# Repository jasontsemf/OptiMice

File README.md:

# OptiMice

## Intro

> "Bespoke computer mice powered by AI and 3D printing"

[Learn more about the project](https://jasontsemf.github.io/optimice.html) on Jason's portfolio site

## Complementary Web Platform

[Live on Back4App](https://optimice-jasontsemf.b4a.run).

[GitHub Repo](https://github.com/jasontsemf/OptimiceDashboard) of the web platform

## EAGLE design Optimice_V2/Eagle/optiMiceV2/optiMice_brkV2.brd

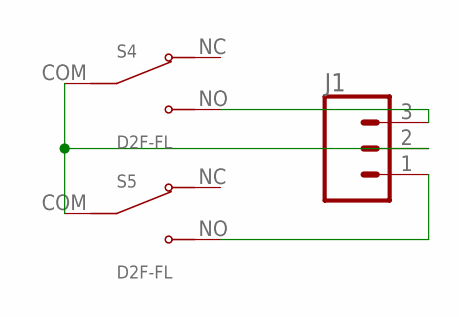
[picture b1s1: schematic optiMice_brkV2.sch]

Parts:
J1: CONN_03JST-PTH-VERT; JST-3-PTH-VERT
S4, S5: D2F-FL; SW_D2F-FL

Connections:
unnamed: J1.2, S4.COM, S5.COM
unnamed: J1.3, S4.NO
unnamed: J1.1, S5.NO

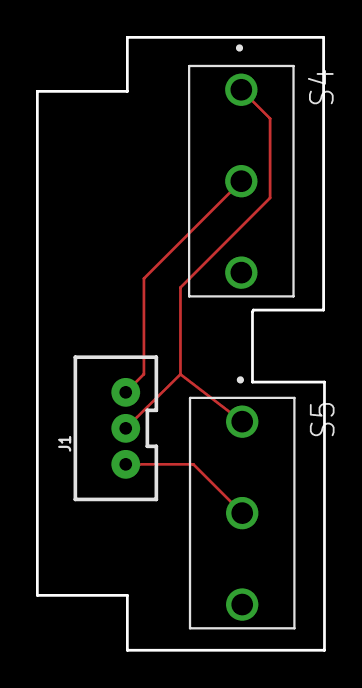
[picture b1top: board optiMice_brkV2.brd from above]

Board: 2 copper layers, 15.9 x 34.0 mm, 3 parts (0 on the bottom side), 3 nets.

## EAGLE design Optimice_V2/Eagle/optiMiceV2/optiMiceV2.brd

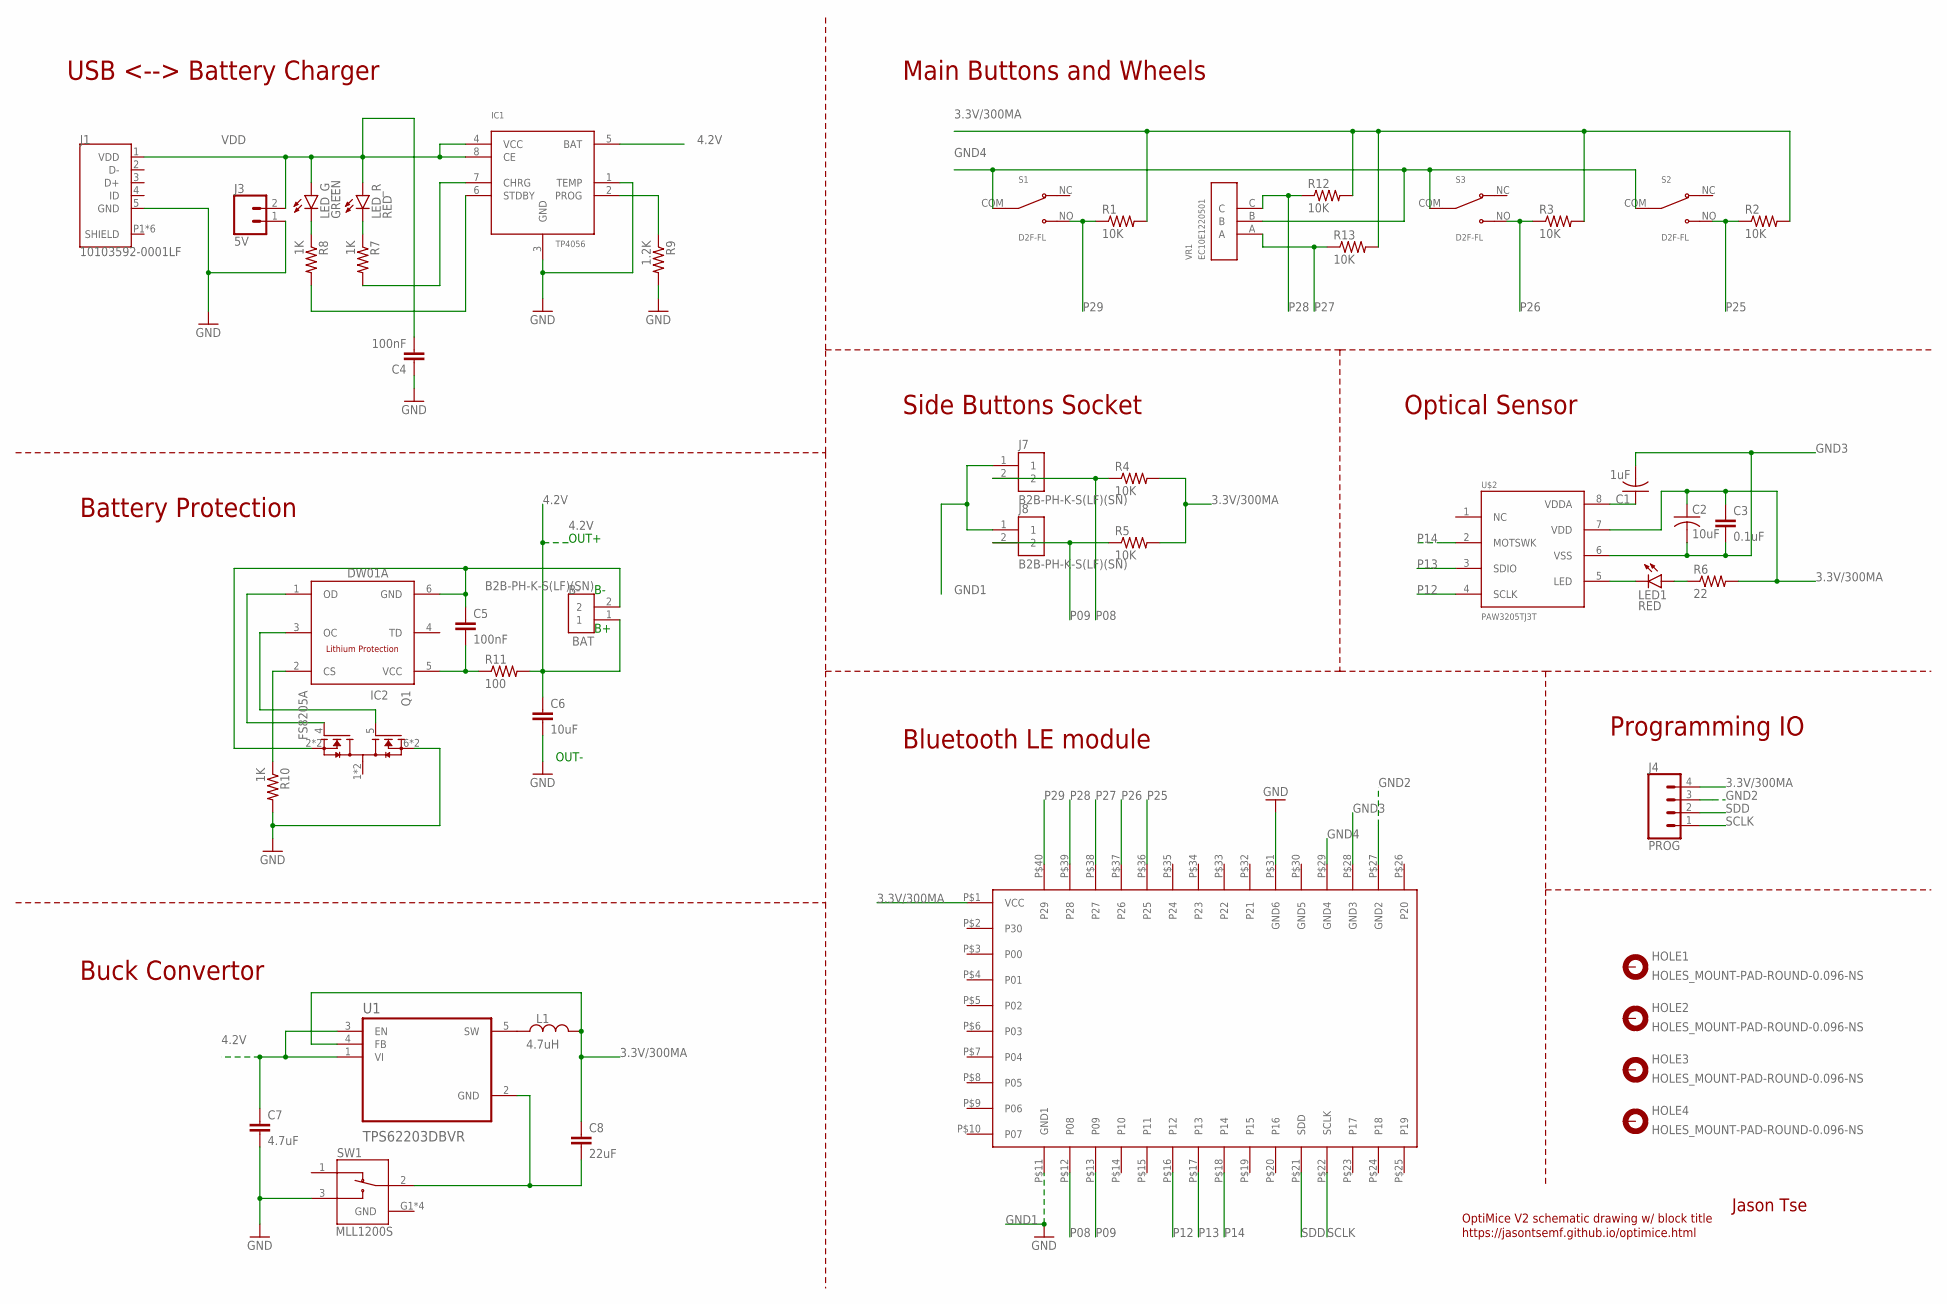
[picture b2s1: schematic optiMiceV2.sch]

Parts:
BAT: B2B-PH-K-S(LF)(SN); JST_B2B-PH-K-S(LF)(SN)
C1: 1uF; C0805K
C2: 10uF; C0805K
C3: 0.1uF; C0805K
C4, C5: 100nF; C0805
C6: 10uF; C0805
C7: 4.7uF; C0805
C8: 22uF; C0805
HOLE1, HOLE2, HOLE3, HOLE4: HOLES_MOUNT-PAD-ROUND-0.096-NS; HOLES_096-PAD-NS
IC1: TP4056; SOP-8
IC2: DW01A; SOT23-6
J1: 10103592-0001LF; AMPHENOL_10103592-0001LF
J3: 5V; 1X02
J4: PROG; 1X04
J7, J8: B2B-PH-K-S(LF)(SN); JST_B2B-PH-K-S(LF)(SN)
L1: 4.7uH; INDC2009X120
LED1: RED; LED5MM
LED_G: GREEN; CHIP-LED0805
LED_R: RED; CHIP-LED0805
Q1: FS8205A; SOP65P640X120-8N
R1, R2, R3, R4, R5, R12, R13: 10K; R0805
R6: 22; R0805
R7, R8, R10: 1K; R0805
R9: 1.2K; R0805
R11: 100; R0805
S1, S2, S3: D2F-FL; SW_D2F-FL
SW1: MLL1200S; SW_MLL1200S
U1: TPS62203DBVR; SOT95P280X145-5N
U$1: NRF51822-02; WT51822-S2
U$2: PAW3205TJ3T; PAW3205
VR1: EC10E1220501; TRIM_EC10E1220501

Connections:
3.3V/300MA: C2.1, C3.1, C8.1, J4.4, L1.2, R1.2, R2.2, R3.2, R4.2, R5.2, R6.2, R12.2, R13.2, U1.4 (FB), U$1.P$1 (VCC), U$2.7 (VDD)
4.2V: BAT.1, C6.1, C7.1, IC1.5 (BAT), R11.2, U1.1 (VI), U1.3 (EN)
B-: BAT.2, C5.1, IC2.6 (GND), Q1.2 (S1), Q1.3 (S1)
GND: C4.1, C6.2, C7.2, IC1.1 (TEMP), IC1.3 (GND), J1.5 (GND), J3.1, Q1.6 (S2), Q1.7 (S2), R9.2, R10.2, SW1.3, SW1.G1 (GND), SW1.G2 (GND), SW1.G3 (GND), SW1.G4 (GND), U$1.P$31 (GND6)
GND1: J7.1, J8.1, U$1.P$11 (GND1)
GND2: J4.3, U$1.P$27 (GND2)
GND3: C1.2, C2.2, C3.2, U$1.P$28 (GND3), U$2.6 (VSS)
GND4: S1.COM, S2.COM, S3.COM, U$1.P$29 (GND4), VR1.B
unnamed: C1.1, U$2.8 (VDDA)
unnamed: LED1.A, R6.1
unnamed: IC1.7 (CHRG), R7.2
unnamed: LED1.K (C), U$2.5 (LED)
unnamed: IC1.6 (STDBY), R8.2
unnamed: LED_R.C, R7.1
unnamed: LED_G.C, R8.1
unnamed: C8.2, SW1.2, U1.2 (GND)
unnamed: IC1.2 (PROG), R9.1
unnamed: L1.1, U1.5 (SW)
unnamed: IC2.3 (OC), Q1.5 (G2)
unnamed: IC2.1 (OD), Q1.4 (G1)
unnamed: C5.2, IC2.5 (VCC), R11.1
unnamed: IC2.2 (CS), R10.1
P08: J7.2, R4.1, U$1.P$12 (P08)
P09: J8.2, R5.1, U$1.P$13 (P09)
P12: U$1.P$16 (P12), U$2.4 (SCLK)
P13: U$1.P$17 (P13), U$2.3 (SDIO)
P14: U$1.P$18 (P14), U$2.2 (MOTSWK)
P25: R2.1, S2.NO, U$1.P$36 (P25)
P26: R3.1, S3.NO, U$1.P$37 (P26)
P27: R13.1, U$1.P$38 (P27), VR1.A
P28: R12.1, U$1.P$39 (P28), VR1.C
P29: R1.1, S1.NO, U$1.P$40 (P29)
SCLK: J4.1, U$1.P$22 (SCLK)
SDD: J4.2, U$1.P$21 (SDD)
SHIELD: J1.P1 (SHIELD), J1.P2 (SHIELD), J1.P3 (SHIELD), J1.P4 (SHIELD), J1.P5 (SHIELD), J1.P6 (SHIELD)
VDD: C4.2, IC1.4 (VCC), IC1.8 (CE), J1.1 (VDD), J3.2, LED_G.A, LED_R.A

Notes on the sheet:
OUT-
OUT+
USB <--> Battery Charger
Battery Protection
Buck Convertor
Side Buttons Socket
Main Buttons and Wheels
Optical Sensor
Programming IO
Bluetooth LE module
Jason Tse
OptiMice V2 schematic drawing w/ block title https://jasontsemf.github.io/optimice.html

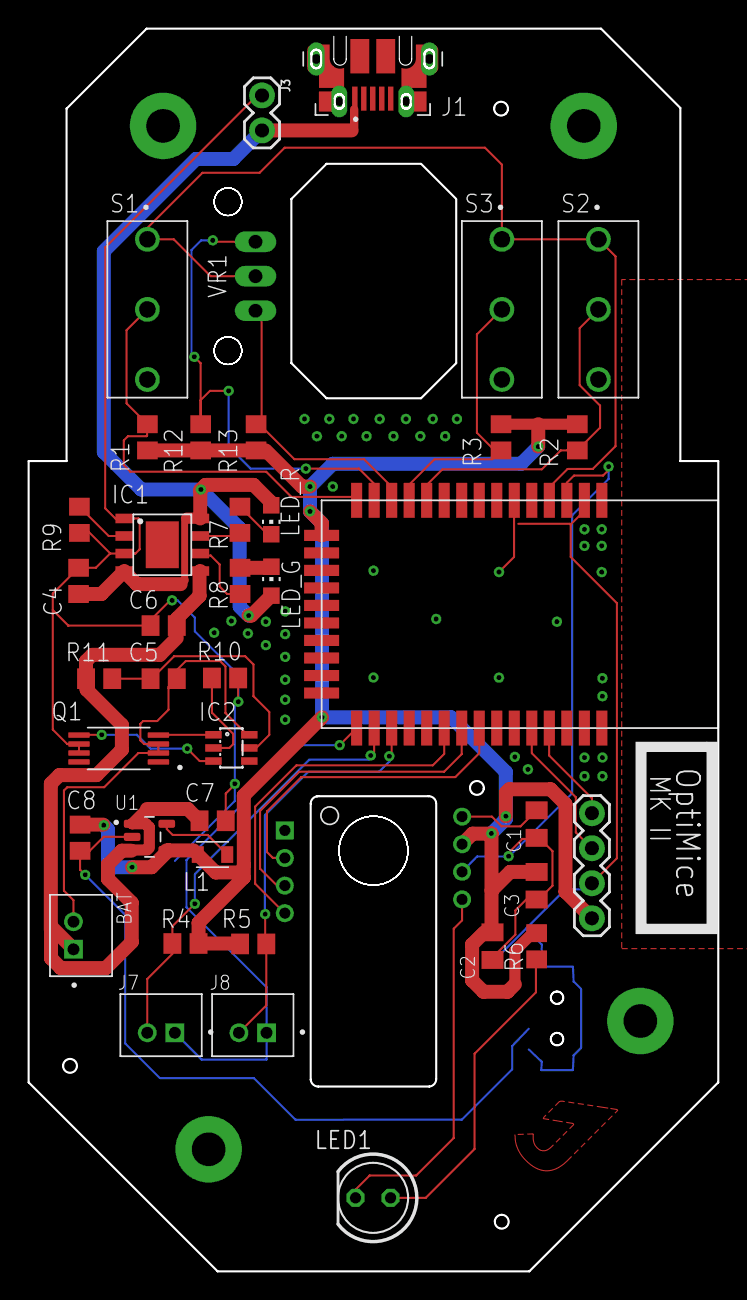
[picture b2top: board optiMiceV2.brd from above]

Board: 2 copper layers, 50.0 x 90.1 mm, 46 parts (1 on the bottom side), 36 nets.

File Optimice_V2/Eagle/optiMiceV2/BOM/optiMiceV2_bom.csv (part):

"Part";"Value";"Device";"Package";"Description";"AVAILABILITY";"BOM";"CATEGORY";"COMMENT";"CURRENT_RATING";"DESCRIPTION";"MANUFACTURER";"MF";"MP";"MPN";"OPERATING_TEMP";"PACKAGE";"PART_STATUS";"POPULARITY";"PRICE";"PROD_ID";"PURCHASE-URL";"ROHS_COMPLIANT";"SERIES";"SPICEPREFIX";"SUB-CATEGORY";"THERMALLOSS";"TYPE";"VALUE";
"BAT";"B2B-PH-K-S(LF)(SN)";"B2B-PH-K-S(LF)(SN)";"JST_B2B-PH-K-S(LF)(SN)";"PH Series 2 Position 2 mm Pitch Through Hole Top Entry Shrouded Header Check prices";"Good";"";"";"";"";" Connector Header Through Hole 2 position 0.079 (2.00mm) ";"";"JST Sales";"B2B-PH-K-S(LF)(SN)";"";"";"None";"";"";"None";"";"https://pricing.snapeda.com/search/part/B2B-PH-K-S(LF)(SN)/?ref=eda";"";"";"";"";"";"";"";
"C1";"1uF";"C-USC0805K";"C0805K";"CAPACITOR, American symbol";"";"";"";"";"";"";"";"";"";"";"";"";"";"19";"";"";"";"";"";"C";"";"";"";"";
"C2";"10uF";"C-USC0805K";"C0805K";"CAPACITOR, American symbol";"";"";"";"";"";"";"";"";"";"";"";"";"";"19";"";"";"";"";"";"C";"";"";"";"";
"C3";"0.1uF";"C-EUC0805K";"C0805K";"CAPACITOR, European symbol";"";"";"";"";"";"";"";"";"";"";"";"";"";"52";"";"";"";"";"";"C";"";"";"";"";
"C4";"100nF";"C-EUC0805";"C0805";"CAPACITOR, European symbol";"";"";"";"";"";"";"";"";"";"";"";"";"";"88";"";"";"";"";"";"C";"";"";"";"";
"C5";"100nF";"C-EUC0805";"C0805";"CAPACITOR, European symbol";"";"";"";"";"";"";"";"";"";"";"";"";"";"88";"";"";"";"";"";"C";"";"";"";"";
"C6";"10uF";"C-EUC0805";"C0805";"CAPACITOR, European symbol";"";"";"";"";"";"";"";"";"";"";"";"";"";"88";"";"";"";"";"";"C";"";"";"";"";
"C7";"4.7uF";"C-EUC0805";"C0805";"CAPACITOR, European symbol";"";"";"";"";"";"";"";"";"";"";"";"";"";"88";"";"";"";"";"";"C";"";"";"";"";
"C8";"22uF";"C-EUC0805";"C0805";"CAPACITOR, European symbol";"";"";"";"";"";"";"";"";"";"";"";"";"";"88";"";"";"";"";"";"C";"";"";"";"";
"HOLE1";"HOLES_MOUNT-PAD-ROUND-0.096-NS";"HOLES_MOUNT-PAD-ROUND-0.096-NS";"HOLES_096-PAD-NS";"MOUNTING PAD, round";"";"EXCLUDE";"";"";"";"";"";"";"";"";"";"";"";"";"";"";"";"";"";"";"";"";"";"";
"HOLE2";"HOLES_MOUNT-PAD-ROUND-0.096-NS";"HOLES_MOUNT-PAD-ROUND-0.096-NS";"HOLES_096-PAD-NS";"MOUNTING PAD, round";"";"EXCLUDE";"";"";"";"";"";"";"";"";"";"";"";"";"";"";"";"";"";"";"";"";"";"";
"HOLE3";"HOLES_MOUNT-PAD-ROUND-0.096-NS";"HOLES_MOUNT-PAD-ROUND-0.096-NS";"HOLES_096-PAD-NS";"MOUNTING PAD, round";"";"EXCLUDE";"";"";"";"";"";"";"";"";"";"";"";"";"";"";"";"";"";"";"";"";"";"";
"HOLE4";"HOLES_MOUNT-PAD-ROUND-0.096-NS";"HOLES_MOUNT-PAD-ROUND-0.096-NS";"HOLES_096-PAD-NS";"MOUNTING PAD, round";"";"EXCLUDE";"";"";"";"";"";"";"";"";"";"";"";"";"";"";"";"";"";"";"";"";"";"";
"IC1";"TP4056";"TP4056";"SOP-8";"";"Unavailable";"";"";"";"";" Complete single cell Li-Ion battery with a constant current / constant voltage linear charger ";"";"NanJing Top Power ASIC Corp.";"TP4056 ";"";"";"Package ";"";"";"None";"";"";"";"";"";"";"";"";"";
"IC2";"DW01A";"DW01A";"SOT23-6";"";"Unavailable";"";"";"";"";" One Cell Lithium-ion/Polymer Battery Protection IC ";"";"Fortune Semiconductor";"DW01A";"";"";"SOT-23-6 Fortune Semiconductor";"";"";"None";"";"";"";"";"";"";"";"";"";
"J1";"10103592-0001LF";"10103592-0001LF";"AMPHENOL_10103592-0001LF";"Conn Micro USB Type B RCP 5 POS 0.65mm Solder RA SMD 5 Terminal 1 Port T/R Check prices";"Good";"";"";"";"";" USB - micro B USB 2.0 Receptacle Connector 5 Position Surface Mount, Right Angle";" Through Hole ";"";"Amphenol ICC (FCI)";"10103592-0001LF";"";"";"None";"";"";"None";"";"https://pricing.snapeda.com/search/part/10103592-0001LF/?ref=eda";"";"";"";"";"";"";
"J3";"5V";"CONN_02";"1X02";"Multi connection point. Often used as Generic Header-pin footprint for 0.1 inch spaced/style header connections";"";"";"";"";"";"";"";"";"";"";"";"";"";"";"";"";"";"";"";"";"";"";"";"";
"J4";"PROG";"CONN_04";"1X04";"Multi connection point. Often used as Generic Header-pin footprint for 0.1 inch spaced/style header connections";"";"";"";"";"";"";"";"";"";"";"";"";"";"";"";"CONN-09696";"";"";"";"";"";"";"";"";
"J7";"B2B-PH-K-S(LF)(SN)";"B2B-PH-K-S(LF)(SN)";"JST_B2B-PH-K-S(LF)(SN)";"PH Series 2 Position 2 mm Pitch Through Hole Top Entry Shrouded Header Check prices";"Good";"";"";"";"";" Connector Header Through Hole 2 position 0.079 (2.00mm) ";"";"JST Sales";"B2B-PH-K-S(LF)(SN)";"";"";"None";"";"";"None";"";"https://pricing.snapeda.com/search/part/B2B-PH-K-S(LF)(SN)/?ref=eda";"";"";"";"";"";"";"";
"J8";"B2B-PH-K-S(LF)(SN)";"B2B-PH-K-S(LF)(SN)";"JST_B2B-PH-K-S(LF)(SN)";"PH Series 2 Position 2 mm Pitch Through Hole Top Entry Shrouded Header Check prices";"Good";"";"";"";"";" Connector Header Through Hole 2 position 0.079 (2.00mm) ";"";"JST Sales";"B2B-PH-K-S(LF)(SN)";"";"";"None";"";"";"None";"";"https://pricing.snapeda.com/search/part/B2B-PH-K-S(LF)(SN)/?ref=eda";"";"";"";"";"";"";"";
"L1";"4.7uH";"L_CHIP-0805(2012-METRIC)";"INDC2009X120";"Inductor Fixed - Generic";"";"";"Inductor";"";"";"";"";"";"";"";"";"";"";"";"";"";"";"";"";"";"Fixed";"";"";"";
"LED1";"RED";"LED5MM";"LED5MM";"LED";"";"";"";"";"";"";"";"";"";"";"";"";"";"93";"";"";"";"";"";"";"";"";"";"";
"LED_G";"GREEN";"LEDCHIP-LED0805";"CHIP-LED0805";"LED";"";"";"";"";"";"";"";"";"";"";"";"";"";"68";"";"";"";"";"";"";"";"";"";"";
"LED_R";"RED";"LEDCHIP-LED0805";"CHIP-LED0805";"LED";"";"";"";"";"";"";"";"";"";"";"";"";"";"68";"";"";"";"";"";"";"";"";"";"";
"Q1";"FS8205A";"FS8205A";"SOP65P640X120-8N";"N/A";"Unavailable";"";"";"";"";" ";"";"Fortune Semiconductor";"FS8205A";"";"";"Package ";"";"";"None";"";"";"";"";"";"";"";"";"";
"R1";"10K";"R-US_R0805";"R0805";"RESISTOR, American symbol";"";"";"";"";"";"";"";"";"";"";"";"";"";"85";"";"";"";"";"";"R";"";"";"";"";
"R2";"10K";"R-US_R0805";"R0805";"RESISTOR, American symbol";"";"";"";"";"";"";"";"";"";"";"";"";"";"85";"";"";"";"";"";"R";"";"";"";"";
"R3";"10K";"R-US_R0805";"R0805";"RESISTOR, American symbol";"";"";"";"";"";"";"";"";"";"";"";"";"";"85";"";"";"";"";"";"R";"";"";"";"";
"R4";"10K";"R-US_R0805";"R0805";"RESISTOR, American symbol";"";"";"";"";"";"";"";"";"";"";"";"";"";"85";"";"";"";"";"";"R";"";"";"";"";
"R5";"10K";"R-US_R0805";"R0805";"RESISTOR, American symbol";"";"";"";"";"";"";"";"";"";"";"";"";"";"85";"";"";"";"";"";"R";"";"";"";"";
"R6";"22";"R-US_R0805";"R0805";"RESISTOR, American symbol";"";"";"";"";"";"";"";"";"";"";"";"";"";"85";"";"";"";"";"";"R";"";"";"";"";
"R7";"1K";"R-US_R0805";"R0805";"RESISTOR, American symbol";"";"";"";"";"";"";"";"";"";"";"";"";"";"85";"";"";"";"";"";"R";"";"";"";"";
"R8";"1K";"R-US_R0805";"R0805";"RESISTOR, American symbol";"";"";"";"";"";"";"";"";"";"";"";"";"";"85";"";"";"";"";"";"R";"";"";"";"";
"R9";"1.2K";"R-US_R0805";"R0805";"RESISTOR, American symbol";"";"";"";"";"";"";"";"";"";"";"";"";"";"85";"";"";"";"";"";"R";"";"";"";"";
"R10";"1K";"R-US_R0805";"R0805";"RESISTOR, American symbol";"";"";"";"";"";"";"";"";"";"";"";"";"";"85";"";"";"";"";"";"R";"";"";"";"";
"R11";"100";"R-US_R0805";"R0805";"RESISTOR, American symbol";"";"";"";"";"";"";"";"";"";"";"";"";"";"85";"";"";"";"";"";"R";"";"";"";"";
"R12";"10K";"R-US_R0805";"R0805";"RESISTOR, American symbol";"";"";"";"";"";"";"";"";"";"";"";"";"";"85";"";"";"";"";"";"R";"";"";"";"";
"R13";"10K";"R-US_R0805";"R0805";"RESISTOR, American symbol";"";"";"";"";"";"";"";"";"";"";"";"";"";"85";"";"";"";"";"";"R";"";"";"";"";
"S1";"D2F-FL";"D2F-FL";"SW_D2F-FL";"SWITCH SNAP ACTION SPDT 1A 125V Check prices";"Good";"";"";"";"";" SWITCH SNAP ACTION SPDT 1A 125V ";"";"Omron Electronics";"D2F-FL";"";"";"MQFP-44 Omron";"";"";"None";"";"https://pricing.snapeda.com/search/part/D2F-FL/?ref=eda";"";"";"";"";"";"";"";
"S2";"D2F-FL";"D2F-FL";"SW_D2F-FL";"SWITCH SNAP ACTION SPDT 1A 125V Check prices";"Good";"";"";"";"";" SWITCH SNAP ACTION SPDT 1A 125V ";"";"Omron Electronics";"D2F-FL";"";"";"MQFP-44 Omron";"";"";"None";"";"https://pricing.snapeda.com/search/part/D2F-FL/?ref=eda";"";"";"";"";"";"";"";
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
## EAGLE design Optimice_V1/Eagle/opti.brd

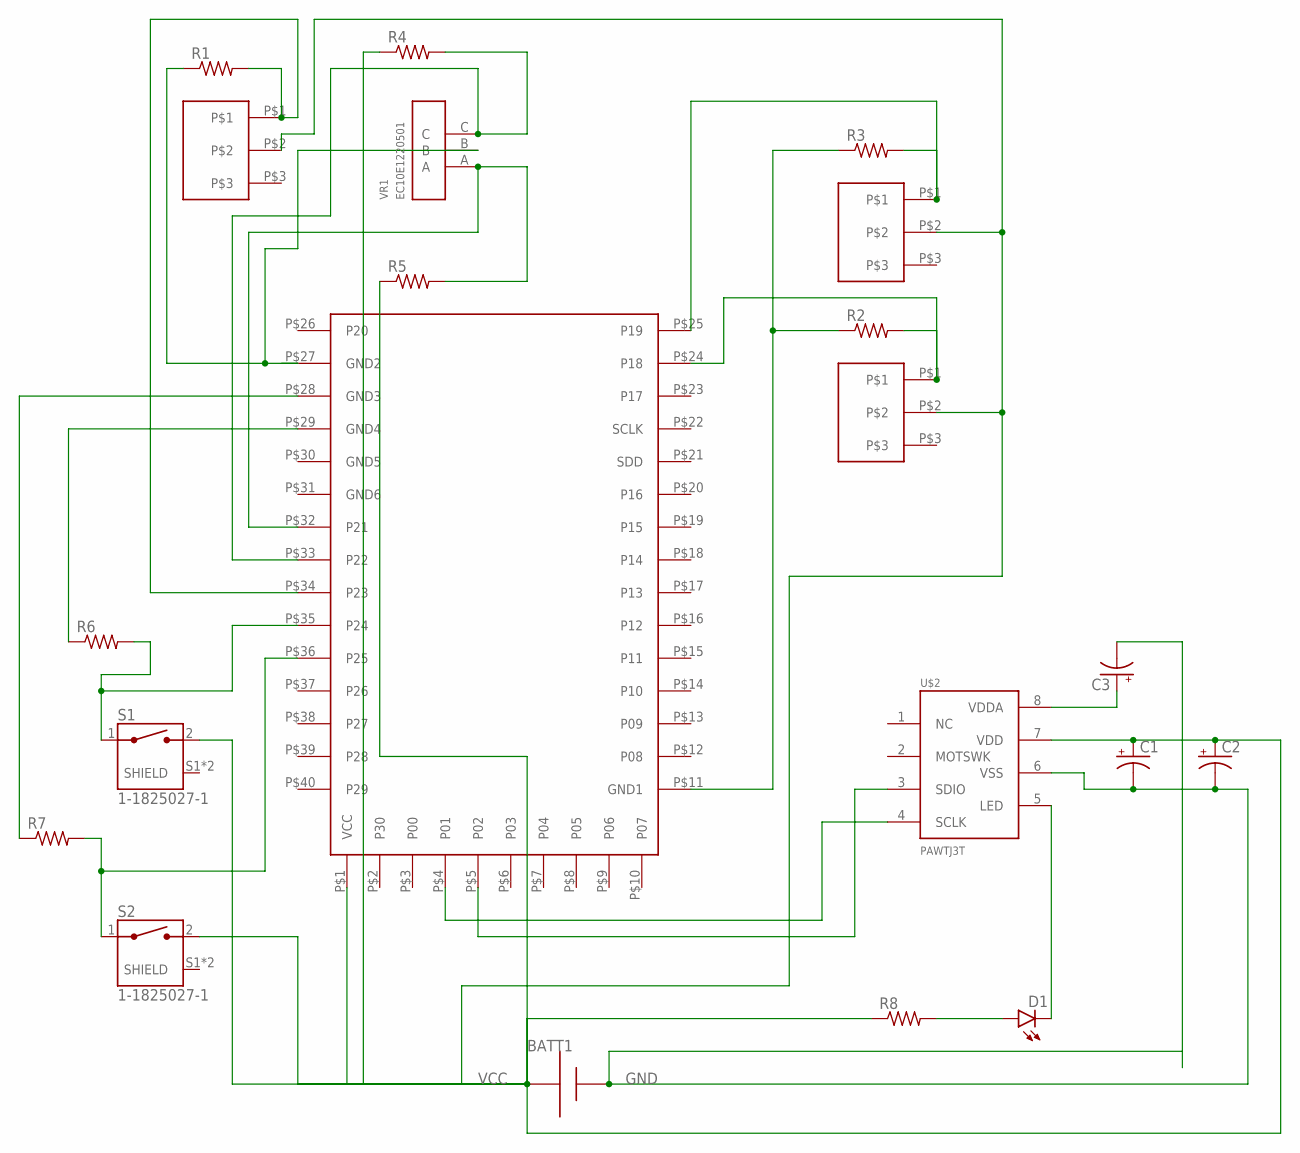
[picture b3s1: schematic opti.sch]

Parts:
BATT1: AAA; 12BH412
C1, C2, C3: CAPACITOR-PE2-5; E2-5
D1: BEAGLEBONE_BLUE_LED-3MM-NO_SILK; BEAGLEBONE_BLUE_BEAGLEBONE_BLUE_LED3MM-NS
R1, R2, R3, R4, R5, R6, R7, R8: R-US_0207/10; 0207/10
S1, S2: 1-1825027-1; SW_1-1825027-1
U$1: NRF51822-02; WT51822-S2
U$2: PAWTJ3T; ADNS-2080
U$3, U$4, U$5: D2FC
VR1: EC10E1220501; TRIM_EC10E1220501

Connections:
GND: BATT1.+, C1.-, C2.-, C3.-, U$2.6 (VSS)
unnamed: U$1.P$5 (P02), U$2.3 (SDIO)
unnamed: U$1.P$4 (P01), U$2.4 (SCLK)
unnamed: C3.+, U$2.8 (VDDA)
unnamed: R3.2, U$1.P$25 (P19), U$5.P$1
unnamed: R2.2, U$1.P$24 (P18), U$4.P$1
unnamed: R2.1, R3.1, U$1.P$11 (GND1)
unnamed: R4.2, U$1.P$33 (P22), VR1.C
unnamed: R5.2, U$1.P$32 (P21), VR1.A
unnamed: R6.2, S1.1, U$1.P$35 (P24)
unnamed: R7.2, S2.1, U$1.P$36 (P25)
unnamed: R1.1, U$1.P$27 (GND2), VR1.B
unnamed: R1.2, U$1.P$34 (P23), U$3.P$1
unnamed: R7.1, U$1.P$28 (GND3)
unnamed: R6.1, U$1.P$29 (GND4)
unnamed: D1.K (C), U$2.5 (LED)
unnamed: D1.A, R8.2
SHIELD: S1.S1 (SHIELD), S1.S2 (SHIELD), S2.S1 (SHIELD), S2.S2 (SHIELD)
VCC: BATT1.-, C1.+, C2.+, R4.1, R5.1, R8.1, S1.2, S2.2, U$1.P$1 (VCC), U$2.7 (VDD), U$3.P$2, U$4.P$2, U$5.P$2

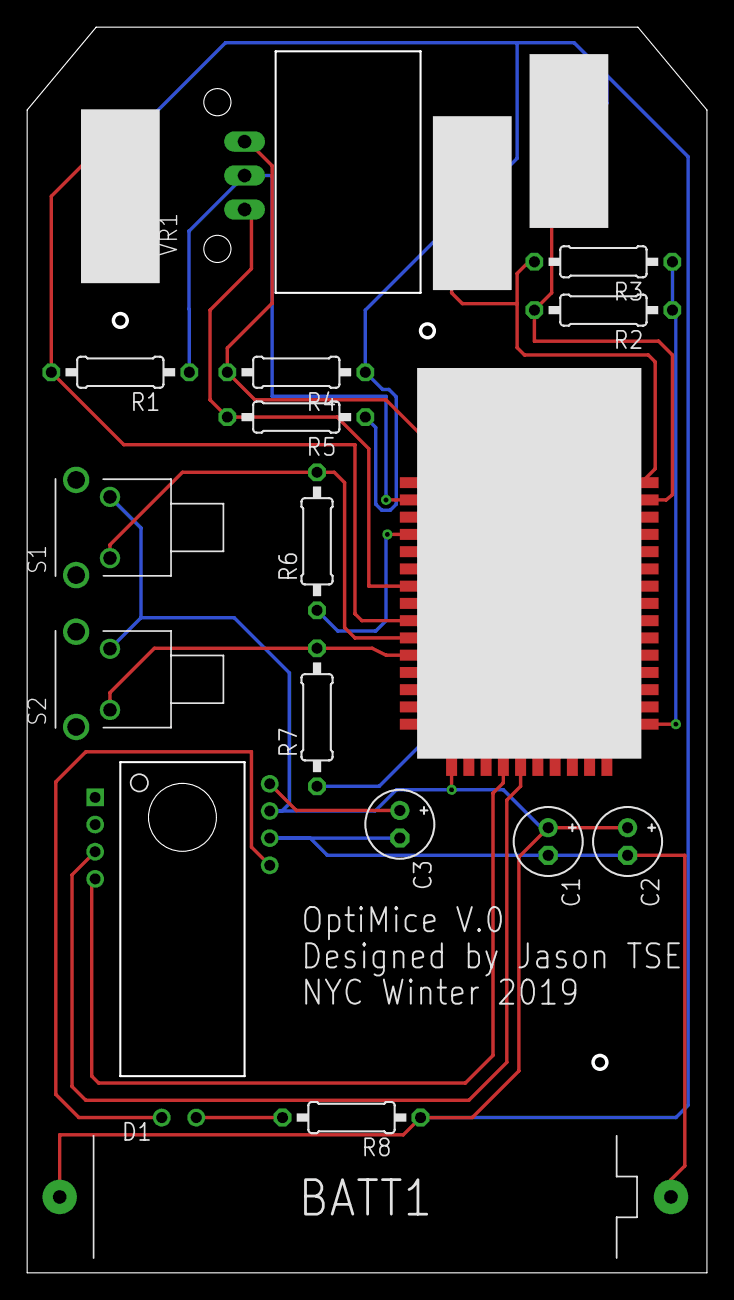
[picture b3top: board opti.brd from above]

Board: 2 copper layers, 49.8 x 91.4 mm, 21 parts (0 on the bottom side), 19 nets.

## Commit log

2019-12-14 minor media update
2020-03-27 major readme update
2020-04-14 minor typo
2020-04-14 added image
2022-03-21 Move all old contents into V1
2022-03-21 Created V2
2022-03-21 Moved minimal hand into v2 software
2022-03-21 meshnet with snapshot 8
2022-03-21 moved in snapshot 12
2022-03-21 moved in snapshot 19
2022-03-21 moved in snapshot 24
2023-07-31 readme update

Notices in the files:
parts and their libraries:
SparkFun-Connectors: Licensing: Creative Commons ShareAlike 4.0 International - https://creativecommons.org/licenses/by-sa/4.0
